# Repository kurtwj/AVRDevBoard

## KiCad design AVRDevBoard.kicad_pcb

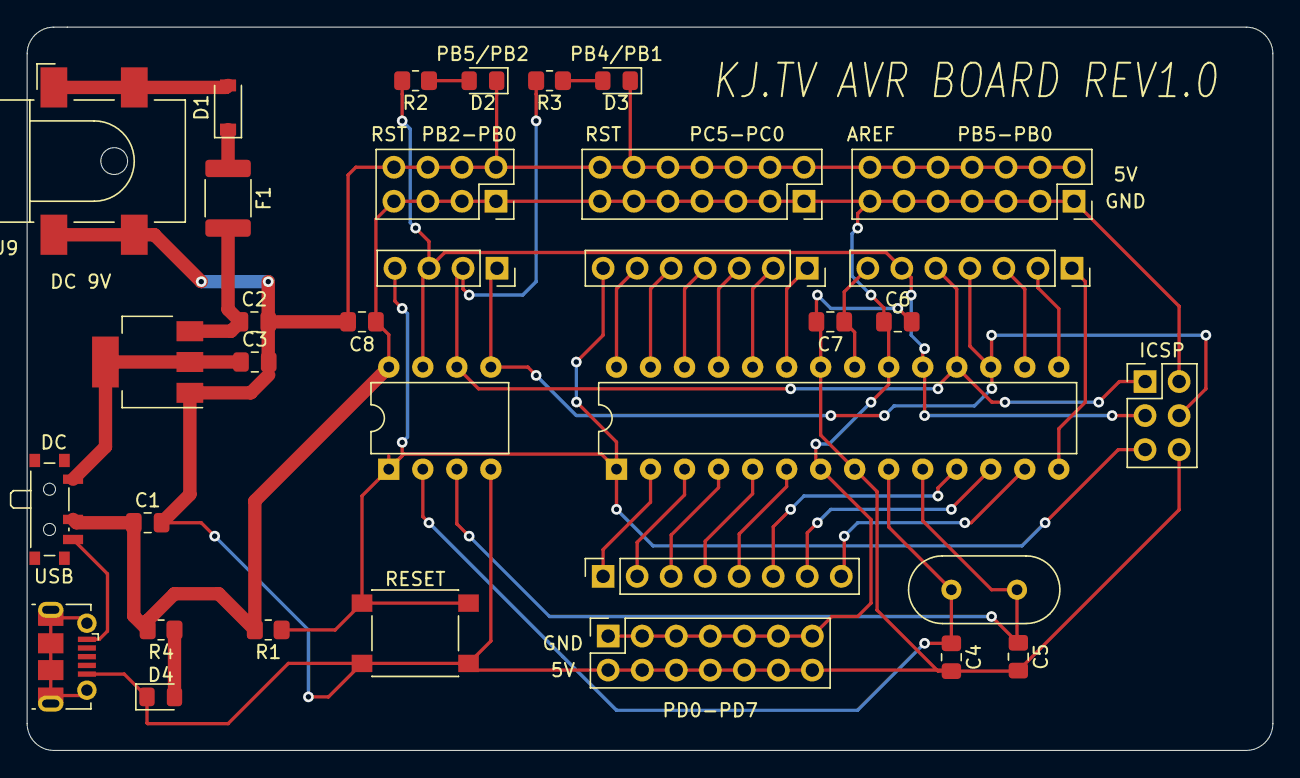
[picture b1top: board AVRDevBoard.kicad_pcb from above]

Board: 2 copper layers, 93.0 x 54.0 mm, 34 parts (0 on the bottom side), 34 nets.

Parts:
C1: 47u; C_0805_2012Metric_Pad1.18x1.45mm_HandSolder
C2, C3: 10u; C_0805_2012Metric_Pad1.18x1.45mm_HandSolder
C4, C5: 22pf; C_0805_2012Metric_Pad1.18x1.45mm_HandSolder
C6, C7, C8: 100n; C_0805_2012Metric_Pad1.18x1.45mm_HandSolder
D1: Diode; D_SOD-123
D2: red; D_0805_2012Metric_Pad1.15x1.40mm_HandSolder
D3, D4: green; D_0805_2012Metric_Pad1.15x1.40mm_HandSolder
F1: 500mA; Fuse_1812_4532Metric_Pad1.30x3.40mm_HandSolder
ICSP: ICSP; PinHeader_2x03_P2.54mm_Vertical
J1: TINY; PinSocket_1x04_P2.54mm_Vertical
J2: powerGND_4; PinSocket_2x04_P2.54mm_Vertical
J3: MEGA_B; PinSocket_1x07_P2.54mm_Vertical
J4: MEGA_C; PinSocket_1x07_P2.54mm_Vertical
J5: MEGA_D; PinSocket_1x08_P2.54mm_Vertical
J6: powerGND_1; PinSocket_2x07_P2.54mm_Vertical
J7: powerGND_2; PinSocket_2x07_P2.54mm_Vertical
J8: powerGND_3; PinSocket_2x07_P2.54mm_Vertical
J9: Barrel_Jack_Switch; BarrelJack_CLIFF_FC681465S_SMT_Horizontal
J10: USB_B_Micro; USB_Micro-B_Molex-105017-0001
R1: 10k; R_0805_2012Metric_Pad1.20x1.40mm_HandSolder
R2, R3, R4: 1k; R_0805_2012Metric_Pad1.20x1.40mm_HandSolder
RESET: resetButton; SW_Push_1P1T_NO_6x6mm_H9.5mm
SW1: powerSwitch; SW_SPDT_PCM12
U1: AMS1117-5.0; SOT-223-3_TabPin2
U2: ATtiny85-20PU; DIP-8_W7.62mm
U3: ATmega328P-PU; DIP-28_W7.62mm
Y1: 16MHz; Crystal_HC18-U_Vertical

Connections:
+5V: C1.1, C6.1, C8.1, ICSP.2, J2.1, J2.3, J2.5, J2.7, J6.1, J6.3, J6.5, J6.7, J6.9, J6.11, J6.13, J7.1, J7.3, J7.5, J7.7, J7.9, J7.11, J7.13, J8.1, J8.3, J8.5, J8.7, J8.9, J8.11, J8.13, R1.2, R4.2, SW1.2, U2.8, U3.7, U3.20
AREF: C7.1, J3.7, U3.21
DC_in: D1.2, J9.1
GND: C1.2, C2.2, C3.2, C4.2, C5.2, C6.2, C7.2, C8.2, D2.1, D3.1, D4.1, ICSP.6, J2.2, J2.4, J2.6, J2.8, J6.2, J6.4, J6.6, J6.8, J6.10, J6.12, J6.14, J7.2, J7.4, J7.6, J7.8, J7.10, J7.12, J7.14, J8.2, J8.4, J8.6, J8.8, J8.10, J8.12, J8.14, J9.2, J9.3, J10.5, RESET.2, U1.1, U2.4, U3.8, U3.22
unnamed: C2.1, F1.2, U1.3
unnamed: C3.1, SW1.1, U1.2
unnamed: D1.1, F1.1
unnamed: D2.2, R2.1
unnamed: D3.2, R3.1
unnamed: D4.2, R4.1
PB0: J3.1, U3.14
PB0_tiny: ICSP.4, J1.1, J3.4, U2.5, U3.17
PB1: J3.2, U3.15
PB1_tiny: ICSP.1, J1.2, J3.5, R3.2, U2.6, U3.18
PB2: J3.3, U3.16
PB2_tiny: ICSP.3, J1.3, J3.6, R2.2, U2.7, U3.19
PC0: J4.1, U3.23
PC1: J4.2, U3.24
PC2: J4.3, U3.25
PC3: J4.4, U3.26
PC4: J4.5, U3.27
PC5: J4.6, U3.28
PD0: J5.1, U3.2
PD1: J5.2, U3.3
PD2: J5.3, U3.4
PD3: J5.4, U3.5
PD4: J5.5, U3.6
PD5: J5.6, U3.11
PD6: J5.7, U3.12
PD7: J5.8, U3.13
RST: ICSP.5, J1.4, J4.7, R1.1, RESET.1, U2.1, U3.1
USB_in: J10.1, SW1.3
XTAL1: C4.1, U2.2, U3.9, Y1.1
XTAL2: C5.1, U2.3, U3.10, Y1.2

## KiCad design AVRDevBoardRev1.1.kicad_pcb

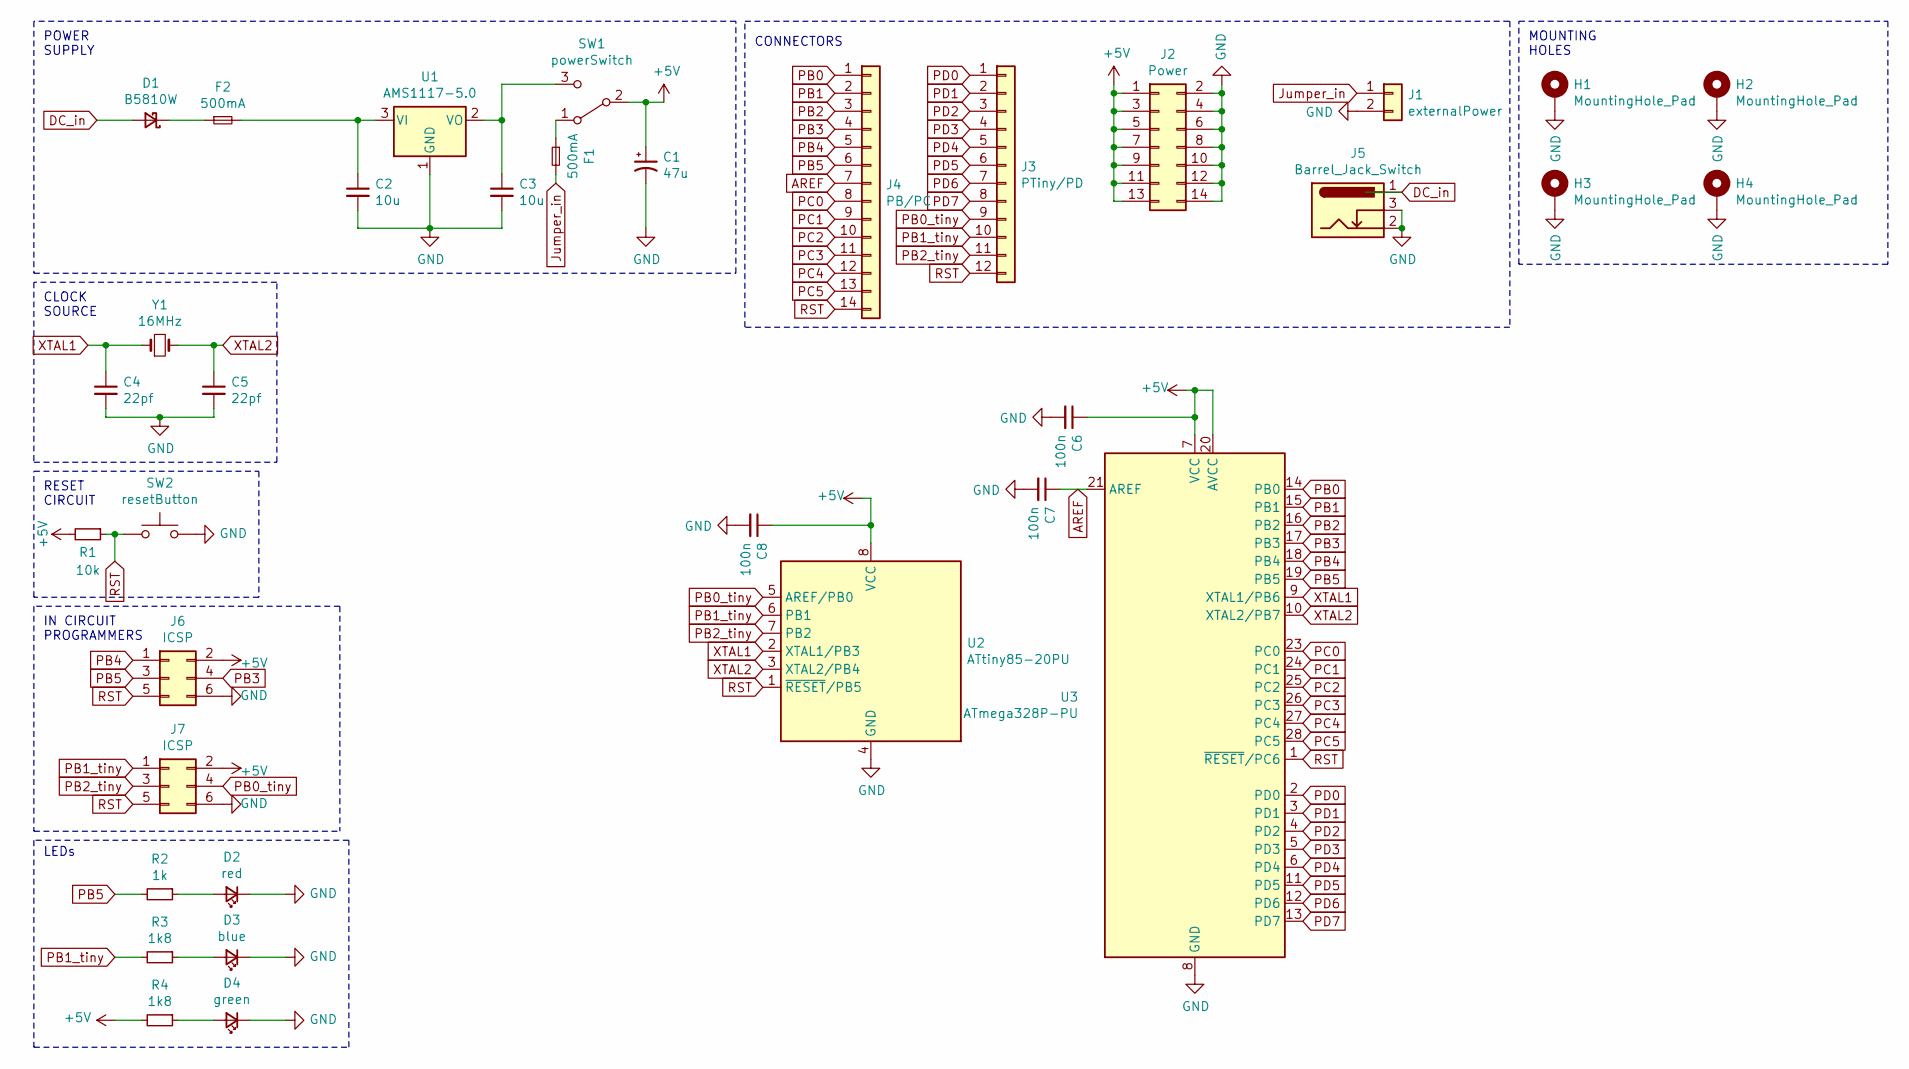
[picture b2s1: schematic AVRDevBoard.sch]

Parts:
C1: 47u; CP_Radial_D10.0mm_P3.50mm
C2, C3: 10u; C_0805_2012Metric_Pad1.18x1.45mm_HandSolder
C4, C5: 22pf; C_0805_2012Metric_Pad1.18x1.45mm_HandSolder
C6, C7, C8: 100n; C_0805_2012Metric_Pad1.18x1.45mm_HandSolder
D1: B5810W; D_SOD-123
D2: red; D_0805_2012Metric_Pad1.15x1.40mm_HandSolder
D3: blue; D_0805_2012Metric_Pad1.15x1.40mm_HandSolder
D4: green; D_0805_2012Metric_Pad1.15x1.40mm_HandSolder
F1, F2: 500mA; Fuse_1812_4532Metric_Pad1.30x3.40mm_HandSolder
H1, H2, H3, H4: MountingHole_Pad; MountingHole_3.2mm_M3_DIN965_Pad
J1: externalPower; PinSocket_1x02_P2.54mm_Vertical
J2: Power; PinSocket_2x07_P2.54mm_Vertical
J3: PTiny/PD; PinSocket_1x12_P2.54mm_Vertical
J4: PB/PC; PinSocket_1x14_P2.54mm_Vertical
J5: Barrel_Jack_Switch; BarrelJack_CLIFF_FC681465S_SMT_Horizontal
J6, J7: ICSP; PinHeader_2x03_P2.54mm_Vertical
R1: 10k; R_1206_3216Metric_Pad1.30x1.75mm_HandSolder
R2: 1k; R_1206_3216Metric_Pad1.30x1.75mm_HandSolder
R3, R4: 1k8; R_1206_3216Metric_Pad1.30x1.75mm_HandSolder
SW1: powerSwitch; SW_SPDT_PCM12
SW2: resetButton; SW_Push_1P1T_NO_6x6mm_H9.5mm
U1: AMS1117-5.0; SOT-223-3_TabPin2
U2: ATtiny85-20PU; DIP-8_W7.62mm
U3: ATmega328P-PU; DIP-28_W7.62mm
Y1: 16MHz; Crystal_HC18-U_Vertical

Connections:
+5V: C1.1, C6.1, C8.1, J2.1, J2.3, J2.5, J2.7, J2.9, J2.11, J2.13, J6.2, J7.2, R1.2, R4.2, SW1.2 (B), U2.8 (VCC), U3.7 (VCC), U3.20 (AVCC)
AREF: C7.1, J4.7, U3.21 (AREF)
DC_in: D1.2 (A), J5.1
GND: C1.2, C2.2, C3.2, C4.2, C5.2, C6.2, C7.2, C8.2, D2.1 (K), D3.1 (K), D4.1 (K), H1.1, H2.1, H3.1, H4.1, J1.2, J2.2, J2.4, J2.6, J2.8, J2.10, J2.12, J2.14, J5.2, J5.3, J6.6, J7.6, SW2.2, U1.1 (GND), U2.4 (GND), U3.8 (GND), U3.22 (GND)
Jumper_in: F1.2, J1.1
unnamed: C2.1, F2.2, U1.3 (VI)
unnamed: C3.1, SW1.3 (C), U1.2 (VO)
unnamed: D1.1 (K), F2.1
unnamed: D2.2 (A), R2.1
unnamed: D3.2 (A), R3.1
unnamed: D4.2 (A), R4.1
unnamed: F1.1, SW1.1 (A)
PB0: J4.1, U3.14 (PB0)
PB0_tiny: J3.9, J7.4, U2.5 (AREF/PB0)
PB1: J4.2, U3.15 (PB1)
PB1_tiny: J3.10, J7.1, R3.2, U2.6 (PB1)
PB2: J4.3, U3.16 (PB2)
PB2_tiny: J3.11, J7.3, U2.7 (PB2)
PB3: J4.4, J6.4, U3.17 (PB3)
PB4: J4.5, J6.1, U3.18 (PB4)
PB5: J4.6, J6.3, R2.2, U3.19 (PB5)
PC0: J4.8, U3.23 (PC0)
PC1: J4.9, U3.24 (PC1)
PC2: J4.10, U3.25 (PC2)
PC3: J4.11, U3.26 (PC3)
PC4: J4.12, U3.27 (PC4)
PC5: J4.13, U3.28 (PC5)
PD0: J3.1, U3.2 (PD0)
PD1: J3.2, U3.3 (PD1)
PD2: J3.3, U3.4 (PD2)
PD3: J3.4, U3.5 (PD3)
PD4: J3.5, U3.6 (PD4)
PD5: J3.6, U3.11 (PD5)
PD6: J3.7, U3.12 (PD6)
PD7: J3.8, U3.13 (PD7)
RST: J3.12, J4.14, J6.5, J7.5, R1.1, SW2.1, U2.1 (~RESET~/PB5), U3.1 (~RESET~/PC6)
XTAL1: C4.1, U2.2 (XTAL1/PB3), U3.9 (XTAL1/PB6), Y1.1
XTAL2: C5.1, U2.3 (XTAL2/PB4), U3.10 (XTAL2/PB7), Y1.2

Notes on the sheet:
POWER SUPPLY
CLOCK SOURCE
RESET CIRCUIT
IN CIRCUIT PROGRAMMERS
CONNECTORS
LEDs
MOUNTING HOLES

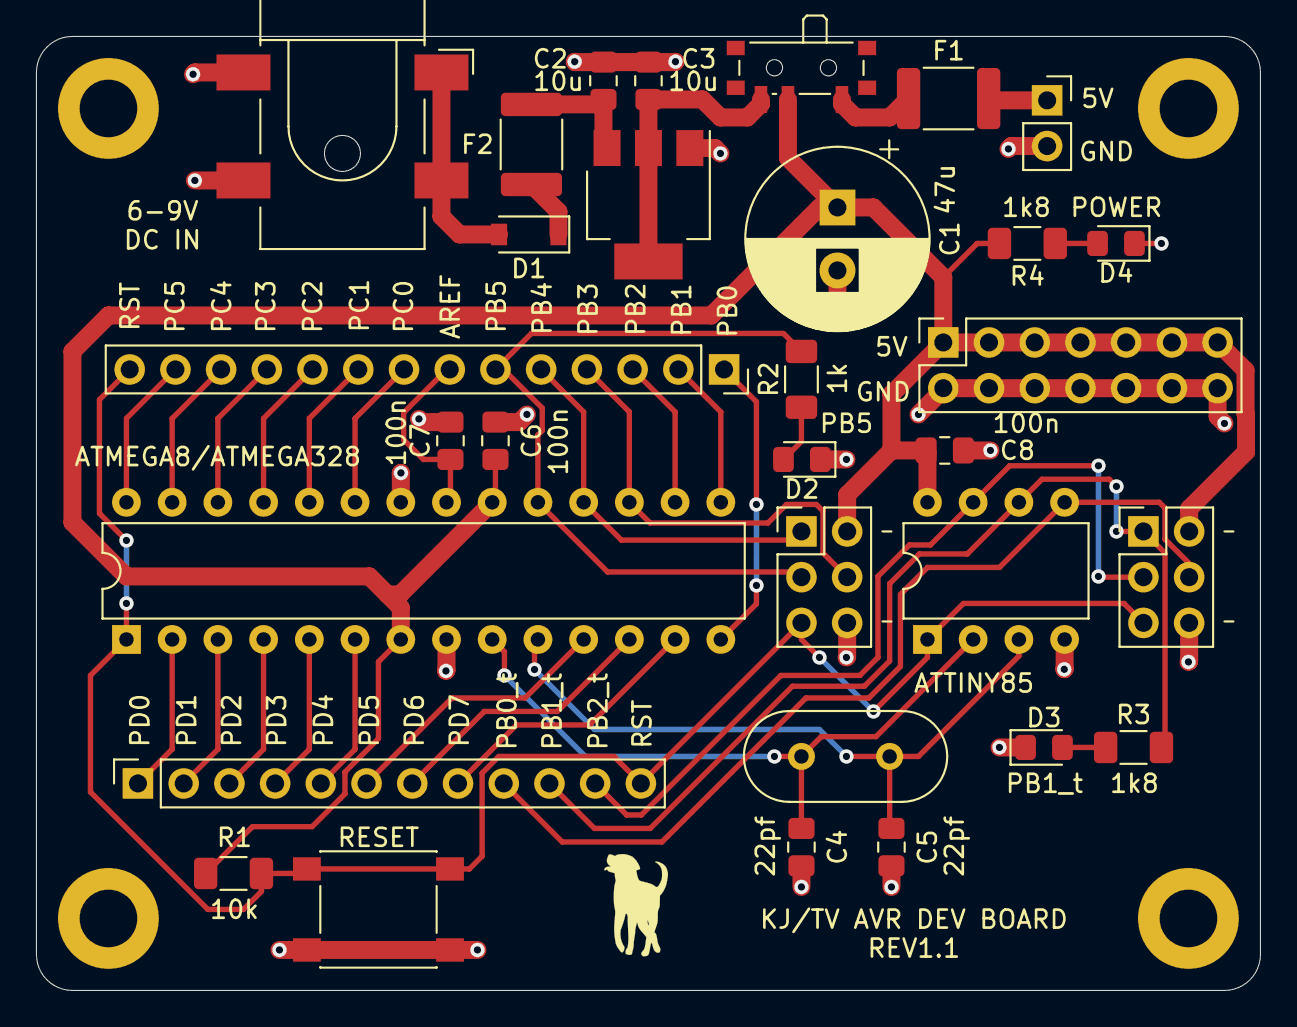
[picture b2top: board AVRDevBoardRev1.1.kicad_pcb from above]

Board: 2 copper layers, 68.0 x 53.0 mm, 35 parts (0 on the bottom side), 38 nets.

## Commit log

2021-07-08 Added dog logo, added microcontroller silkscreen labels, shipped to jlcpcb
